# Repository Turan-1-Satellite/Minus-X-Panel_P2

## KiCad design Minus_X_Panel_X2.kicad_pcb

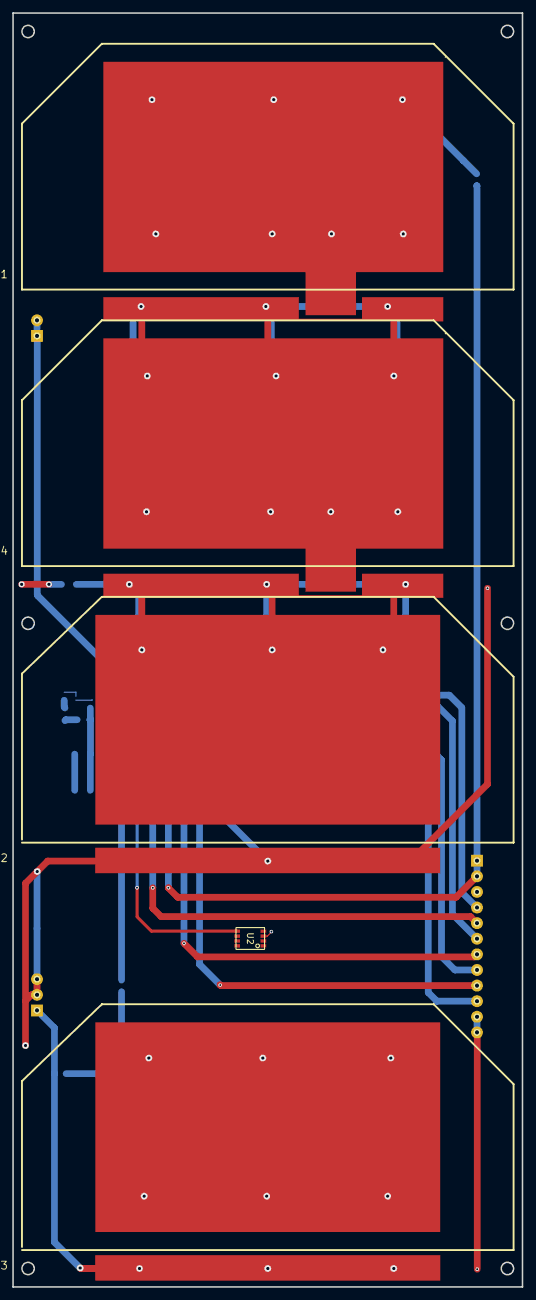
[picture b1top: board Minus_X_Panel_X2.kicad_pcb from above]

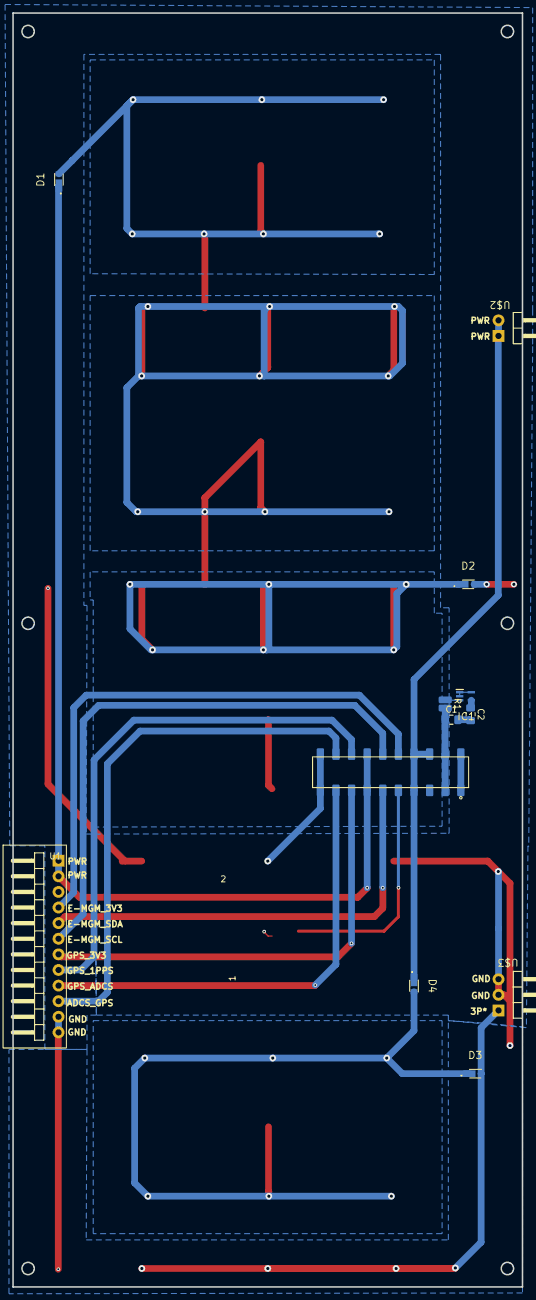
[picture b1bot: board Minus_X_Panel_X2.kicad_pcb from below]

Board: 4 copper layers, 82.9 x 207.3 mm, 17 parts (12 on the bottom side), 19 nets.

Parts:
C1, C2: 1uF; C_0805_2012Metric_Pad1.18x1.45mm_HandSolder
D1, D2, D3, D4: CUHS20S30,H3F
IC1: LMT84DCKT
R1: 1k; R_0508_1220Metric_Pad1.12x2.15mm_HandSolder
S1, S4: solar_cell_B
S2, S3: Solar_cell_C; solar_cell_C
U1: FSR-41057-12
U2: S16008-33
U3: FSM-42052-10
U$2: 2PIN_MALE; PSR-410253-02-M
U$3: 3PIN_MALE3PIN_MALE; PSR-410253-03-M

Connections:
/+V2A: D2.1 (K), S2.+V, S4.GND
/+V2B: S1.GND, S4.+V
/+V2C: D1.2 (A), S1.+V
/+V2D: D3.1 (K), D4.2 (A), S3.+V
/ADCS_GPS: U1.10 (ADCS_GPS), U3.18 (PIN)
/E-MGM_3V3: U1.4 (E-MGM_3V3), U3.10 (PIN)
/E-MGM_SCL: U1.6 (E-MGM_SCL), U3.12 (PIN)
/E-MGM_SDA: U1.5 (E-MGM_SDA), U3.11 (PIN)
/GPS_1PPS: U1.8 (GPS_1PPS), U3.16 (PIN)
/GPS_3V3: U1.7 (GPS_3V3), U3.15 (PIN)
/GPS_ADCS: U1.9 (GPS_ADCS), U3.17 (PIN)
/PWR_P1: D1.1 (K), U1.1 (PWR), U1.2 (PWR), U3.13 (PIN), U3.14 (PIN)
/PWR_P*: D4.1 (K), U3.6 (PIN), U3.7 (PIN), U3.8 (PIN), U$2.1PWR, U$2.2PWR
/TEMP_-X: C1.1, R1.2, U3.3 (PIN), U3.4 (PIN)
GND: C1.2, C2.2, D2.2 (A), IC1.1 (GND1), IC1.2 (GND2), IC1.5 (GND3), S2.GND, U1.11 (GND), U1.12 (GND), U2.3 (ANODE), U3.1 (GND), U3.2 (GND), U3.19 (GND), U3.20 (GND), U$3.1GND, U$3.GND
unnamed: D3.2 (A), S3.GND, U$3.3P*
unnamed: IC1.3 (OUT), R1.1
unnamed: C2.1, IC1.4 (VDD)
unnamed: U2.5 (CATHODE), U3.9 (PIN)

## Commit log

2026-04-15 Panel Design
